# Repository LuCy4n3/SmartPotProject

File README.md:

# SmartPot / GreenGrowTech

An experimental smart plant-pot system combining a custom AVR board, an Android
app, a SQL Server database, a .NET API, a serial gateway and an optional camera.
The app displays plant and pot information and sends pump, greenhouse and photo
requests through the API to the connected hardware.

[Proof-of-concept video](https://www.youtube.com/watch?v=sH559vDkE20&t=21s&ab_channel=RaulSimonca)

## How the parts connect

```text
Android app <--> SQLserverFinale API <--> SQL Server (PlantsDB)
                         ^
                         | HTTP
                       potHub <--> serial/radio <--> SmartPot AVR board

Camera host <--> board UART; camera host --> API image upload
```

`potHub` is a console serial gateway. Although its project uses the web SDK and
has launch profiles, it does not start an HTTP server.

## Repository layout

| Directory | Contents |
| --- | --- |
| `AndroidApp/` | Java Android app (`com.example.greengrowtechapp`). |
| `SQLserverFinale/` | ASP.NET Core 8 API, Entity Framework models and migrations. |
| `potHub/` | .NET 8 serial-to-HTTP gateway for readings and control commands. |
| `SmartPotV4/` | Atmel/Microchip Studio solution with C and C++ firmware projects. |
| `PCB/` | KiCad board designs, component libraries, modules and manufacturing outputs. |
| `CameraCode/` | Python UART/camera scripts and legacy camera installation references. |
| `Programmer/` | Programming, serial, RS485 and demo utilities, including third-party code. |
| `I2CTests/` | Separate firmware experiments for sensors and I2C. |
| `proj_test/` | Supporting experiments and plant-data tools; not needed for normal startup. |

The root files `BackUpDataBase` and `DatabaseBackUp` are legacy SQL Server backup
files, despite having no extension. They are retained as database restore inputs.

The [SmartPot PCB overview](PCB/SmartPot/README.md) links the current editable
board, the separately preserved 2024-10-09 snapshot and the additional
manufacturing exports supplied with the local PCB collection.

## Requirements

- Windows with the .NET 8 SDK for the API and gateway.
- SQL Server or SQL Server LocalDB, plus a database administration tool such as
  SQL Server Management Studio (SSMS).
- Android Studio with JDK 17 and Android SDK 33. The project uses Android Gradle
  Plugin 8.1.0 and the included Gradle 8.0 wrapper. The app requires Android 12
  (API 31) or later.
- For hardware: the matching SmartPot PCB, serial/radio interface and
  Atmel/Microchip Studio with AVR32DA32 support and a compatible programmer.
- For the optional camera: a compatible Linux camera host, Python 3, an enabled
  UART and a working `libcamera-still` command.

Commands below run from the repository root in PowerShell unless stated otherwise.

## 1. Prepare the database

Restore a suitable root backup into a local database, for example `PlantsDB`.
In SSMS, use **Databases > Restore Database > Device**, browse to the backup file
(select all file types if necessary), and review the source database and file
destinations before restoring into a new database.

The API expects `Plant`, `User` and `Pot` tables. The checked-in migrations include
the original schema and a later change to make `PotId` an identity column. This
repository does not automatically create, migrate or seed the database at startup.
Use a restored database as the initial setup path; inspect migrations before
applying them to an existing database because `PotIdentity` drops and recreates
the `PotId` column.

Verify that the database contains the plant and user records you want to use.
A pot references an existing `PlantName` and `UserId`, and `PotName` must be unique.
Backup contents and record IDs may differ between the two backups.

## 2. Configure and start the API

For a fresh checkout, create the local configuration file once:

```powershell
Copy-Item SQLserverFinale/SQLserverFinale/appsettings.example.json SQLserverFinale/SQLserverFinale/appsettings.json
```

If `appsettings.json` already exists, keep it and edit the connection string for
your database instead. This local file is ignored by Git. The example uses
Windows authentication with LocalDB; use your own SQL Server connection string
when running a different instance.

An environment variable can override the connection string for the current shell:

```powershell
$env:ConnectionStrings__DefaultConnection = 'Server=(localdb)\MSSQLLocalDB;Database=PlantsDB;Integrated Security=True;TrustServerCertificate=True;'
```

Start the API on port 3000:

```powershell
dotnet restore SQLserverFinale/SQLserverFinale/SQLserverFinale.csproj
dotnet run --project SQLserverFinale/SQLserverFinale/SQLserverFinale.csproj --no-launch-profile --urls http://0.0.0.0:3000
```

This overrides the old machine-specific address in `launchSettings.json`. When
using an IDE launch profile instead, update that profile to your server's address.
Allow the chosen TCP port through the host firewall for LAN clients.

Check the running API in a second PowerShell window:

```powershell
Invoke-RestMethod http://localhost:3000/api/Plant
Invoke-RestMethod http://localhost:3000/api/Pot
```

Swagger is currently disabled in `Program.cs`, so `/swagger` is not a startup check.

## 3. Configure and run the Android app

1. Open `AndroidApp/` in Android Studio and let Gradle sync.
2. In `app/src/main/java/com/example/greengrowtechapp/MainActivity.java`, set
   `Url` to `http://<API_HOST>:3000/api/`, including the trailing slash. A physical
   phone needs the API computer's LAN address; `localhost` refers to the phone.
   The Android emulator normally reaches the host through `10.0.2.2`.
3. In `app/src/main/res/xml/network_security_config.xml`, add the same host
   without a scheme or port to the domains allowed to use HTTP.
4. Set `indexOfCurrentUser` to an existing database user. Its current source
   default is `303`; this must match the gateway's user for an integrated setup.
5. Ensure that user has at least one pot before starting the app: startup reads
   the first pot returned for that user. Set the initial pot ID consistently in
   `MainActivity.java` if needed.
6. Run the app on an Android 12+ phone or emulator. Use the plant/pot screens to
   view records, select a pot and send control requests.

You can also build a debug APK from PowerShell:

```powershell
Push-Location AndroidApp
.\gradlew.bat assembleDebug
Pop-Location
```

The APK is written to `AndroidApp/app/build/outputs/apk/debug/app-debug.apk`.

## 4. Configure the board and serial gateway

Open `SmartPotV4/SmartPotV4.atsln` in Atmel/Microchip Studio. The fuller sensor and
control implementation is `SmartPotV4_Cpp`; the sibling `SmartPotV4` C project
contains test code. Select the intended project explicitly before building or
flashing. Verify the target, board connections and programmer against the PCB.

In `SmartPotV4/SmartPotV4_Cpp/main.cpp`, `INDEX` is the pot identifier and `TYPE`
is the hardware type. The source currently uses `INDEX = 4` and `TYPE = 2`.
Match the firmware's pot ID to the database record. Do not assume a newly created
identity value equals the firmware's ID.

Before starting the gateway, edit `potHub/potHub/Program.cs`:

- Set `SerialPortStream("COM22", 9600)` to the actual interface and matching baud rate.
- Set **all four** `httpClient.BaseAddress` assignments to the API address, for
  example `http://localhost:3000` when both programs run on the same computer.
- Align `USER`, literal `UserId = 1` assignments and the hard-coded
  `/api/Pot/1/{index}` request with the Android user's database ID. Changing
  `USER` alone does not update all of these values.

These settings are currently in source code; the gateway does not read them from
`appsettings.json` or environment variables.

```powershell
dotnet restore potHub/potHub/potHub.csproj
dotnet run --project potHub/potHub/potHub.csproj --no-launch-profile
```

Start the API first, connect the serial interface, then start the gateway. The
gateway waits for the board's identification data. If it stays at `Looking for
data.`, check the serial port, baud rate and board transmission; reset the board
after opening the gateway if its startup identification was missed.

## 5. Optional camera

On the Linux camera host, confirm `libcamera-still` can capture a photo and the
UART is enabled. In `CameraCode/startup_uart.py`, set the serial device (currently
`/dev/ttyAMA0`, 9600 baud) and upload URL to your setup. The upload endpoint is
`http://<API_HOST>:3000/api/image/upload`.

Run from `CameraCode/` on that host:

```bash
python3 -m venv .venv
source .venv/bin/activate
python -m pip install -r requirements.txt
python startup_uart.py
```

This script reacts to UART bytes `0x15 0x01 0x05`, captures `test.jpg`, and uploads
it as multipart field `image`. The older `finalScript.py` checks decimal `15`
(`0x0F`) as its header instead, so these scripts are not interchangeable. Match
the script to the board's camera command; this needs hardware verification.
An uploaded `test.jpg` is available at `/api/image/test.jpg`.

The camera installation script and link lists are legacy hardware references.
Use a camera stack compatible with the actual camera and OS; the old ARM64 `.deb`
downloads are kept locally when cleaning an existing checkout and are ignored by Git.

## Troubleshooting and current limits

| Symptom | Check |
| --- | --- |
| API fails on database access | SQL instance, database restore, connection string and table names. |
| Phone cannot reach API | API host/port, LAN connection, firewall and Android HTTP domain list. |
| No pots or startup error in app | Existing user ID and at least one associated pot. |
| Gateway cannot open serial port | Correct device, port permissions and another program holding the port. |
| Readings or controls target the wrong pot | Firmware `INDEX`, database `PotId` and user IDs in every client. |
| Photo never arrives | Camera UART command/header, capture command and upload URL. |

This is a prototype with hard-coded network addresses and IDs. The current API
handles user passwords directly and does not implement production authentication;
use test accounts on a trusted development network. Camera integration and the
experimental NPK/SPI paths need verification on the target hardware. No end-to-end
hardware validation is implied by the repository cleanup.

## Git and local files

Track source code, project definitions, migrations, PCB designs and required
libraries. Build outputs, IDE state, camera-host home files, installed Python
packages, caches, KiCad locks/backups and local configuration are ignored.

For an existing checkout, cleanup removes generated and local files from Git's
index while leaving their working copies in place. The large
`Programmer/iot-sunxi-driver/` source tree is third-party code and is retained
with its original documentation and license. The original README also identifies
`Programmer/` as externally sourced; verify attribution before redistributing it.

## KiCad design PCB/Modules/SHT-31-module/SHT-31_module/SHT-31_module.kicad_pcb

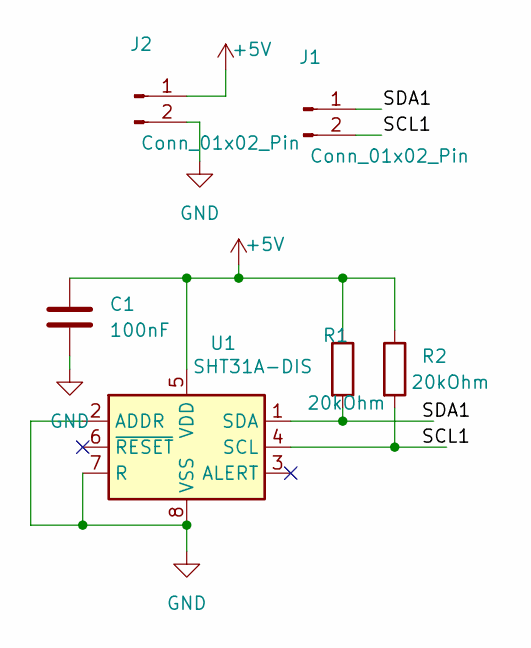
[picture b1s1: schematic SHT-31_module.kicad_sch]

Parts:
C1: 100nF; C_1206_3216Metric
J1, J2: Conn_01x02_Pin; PinHeader_1x02_P2.54mm_Vertical
R1, R2: 20kOhm; R_1206_3216Metric_Pad1.30x1.75mm_HandSolder
U1: SHT31A-DIS; Sensirion_DFN-8-1EP_2.5x2.5mm_P0.5mm_EP1.1x1.7mm

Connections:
+5V: C1.1, J2.1, R1.1, R2.1, U1.5 (VDD)
/SCL1: J1.2, R2.2, U1.4 (SCL)
/SDA1: J1.1, R1.2, U1.1 (SDA)
GND: C1.2, J2.2, U1.2 (ADDR), U1.7 (R), U1.8 (VSS), U1.9 (VSS)

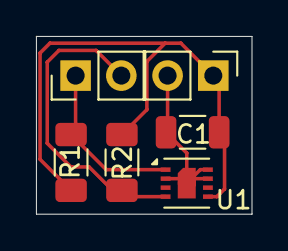
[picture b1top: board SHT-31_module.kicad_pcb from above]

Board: 2 copper layers, 12.0 x 9.9 mm, 6 parts (0 on the bottom side), 4 nets.

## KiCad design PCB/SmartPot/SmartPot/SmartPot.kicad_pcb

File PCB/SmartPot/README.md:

# SmartPot PCB files

| Location | Contents |
| --- | --- |
| [Current editable project](SmartPot/SmartPot.kicad_pro) | Existing tracked SmartPot schematic and PCB. |
| [2024-10-09 snapshot](revisions/2024-10-09/SmartPot.kicad_pro) | Editable schematic, PCB and project imported from the dated local backup. |
| `manufacturing/imported/GERBER/` | Additional supplied SmartPot manufacturing export. |
| `manufacturing/imported/grb/` | Additional supplied SmartPot manufacturing export and drill files. |
| `manufacturing/imported/drill/` | Supplied standalone plated/non-plated drill files. |

The dated snapshot differs from the current design and is kept separately.
The original tracked board was not overwritten. The manufacturing sets are
preserved as supplied; their correspondence to a particular editable revision
has not been established. Regenerate manufacturing output from the chosen PCB
revision when preparing a new fabrication run.

The snapshot comes from `SmartPot-2024-10-09_225239.zip`. The native source
filenames remain `SmartPot.kicad_pro`, `SmartPot.kicad_sch` and `SmartPot.kicad_pcb`.
Open the project file for the revision you want to inspect in KiCad.

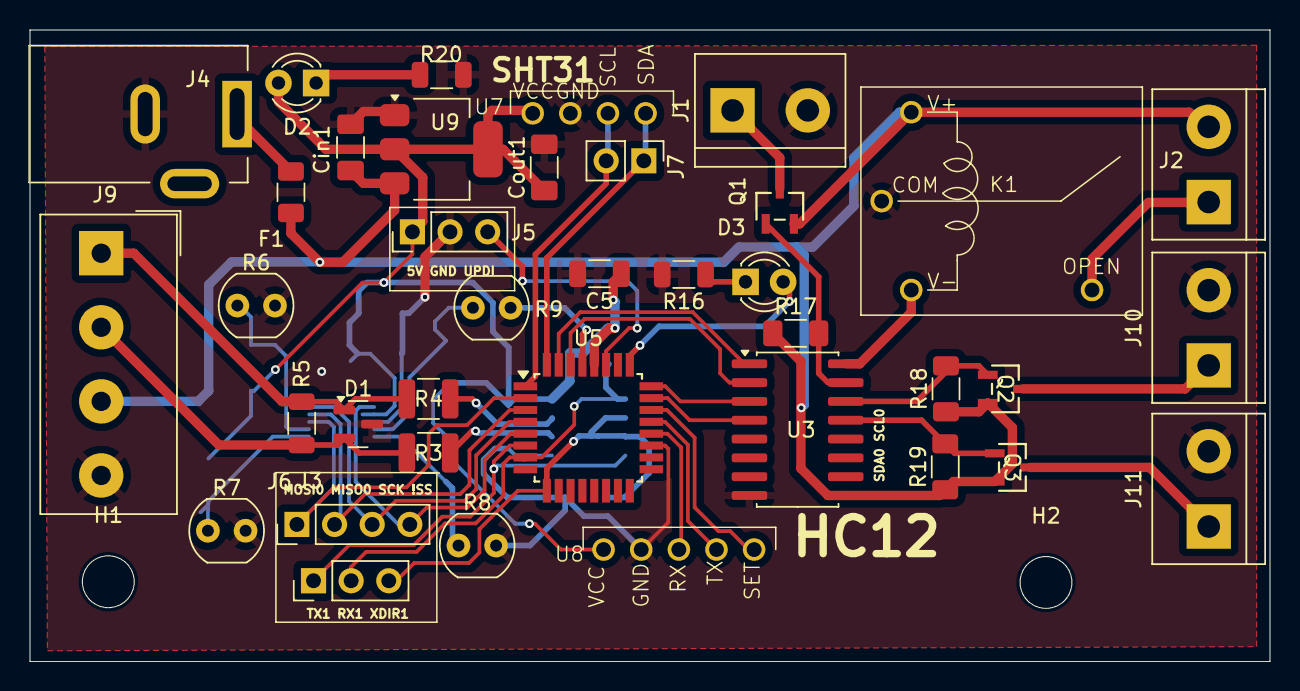
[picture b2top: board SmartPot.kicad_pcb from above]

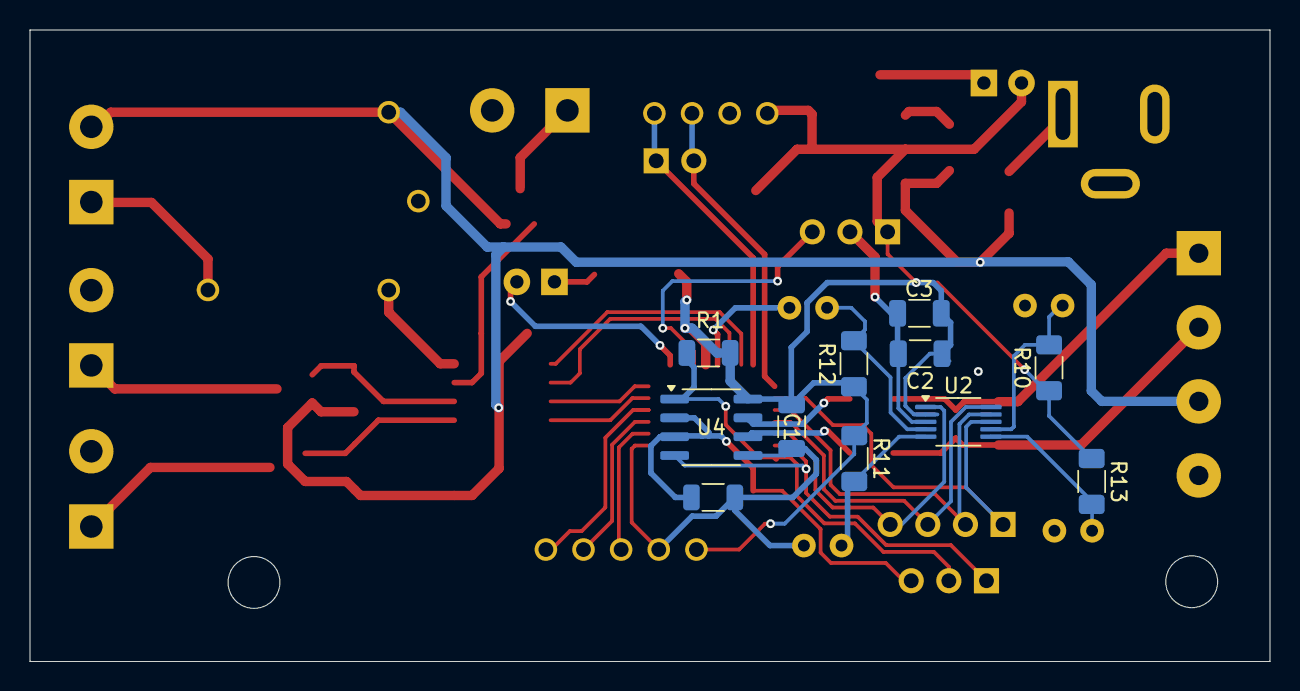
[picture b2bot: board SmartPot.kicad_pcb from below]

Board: 2 copper layers, 83.7 x 42.6 mm, 51 parts (11 on the bottom side), 40 nets.

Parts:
C1: 100nF; C_1206_3216Metric
C2: 0.1uF; C_1206_3216Metric
C3: 10uF; C_1206_3216Metric
C5: 1uF; C_1206_3216Metric
Cin1: 100nF; C_1206_3216Metric_Pad1.33x1.80mm_HandSolder
Cout1: 10uF; C_1206_3216Metric_Pad1.33x1.80mm_HandSolder
D1: SM712_SOT23; SOT-23
D2, D3: LED; LED_D3.0mm_FlatTop
F1: Fuse; Fuse_1206_3216Metric
H1, H2: MountingHole; MountingHole_3.5mm
J1, J2, J10, J11: Screw_Terminal_01x02; TerminalBlock_bornier-2_P5.08mm
J3, J5: Conn_01x03_Pin; PinHeader_1x03_P2.54mm_Vertical
J4: Barrel_Jack_MountingPin; BarrelJack_Kycon_KLDX-0202-xC_Horizontal
J6: Conn_01x04_Pin; PinHeader_1x04_P2.54mm_Vertical
J7: Conn_01x02_Pin; PinHeader_1x02_P2.54mm_Vertical
J9: Screw_Terminal_01x04; Altech_AK100_1x04_P5.00mm
K1: AWHSH112DM00G
Q1, Q2, Q3: SSM3J352F_LF; S-MINI_TOS
R1, R2: 10kOhm; R_1206_3216Metric
R3, R4: 10Ohm; R_1210_3225Metric
R5: 120; R_1206_3216Metric
R6, R7, R8, R9: R_Photo; R_LDR_4.9x4.2mm_P2.54mm_Vertical
R10, R17, R18, R19: 10kohm; R_1206_3216Metric_Pad1.30x1.75mm_HandSolder
R11, R13: 56.2kOhm; R_1206_3216Metric_Pad1.30x1.75mm_HandSolder
R12: 10kOhm; R_1206_3216Metric_Pad1.30x1.75mm_HandSolder
R16, R20: 250-400 Ohm; R_1206_3216Metric
U2: ADC084S021CIMM/NOPB; VSSOP-10_3x3mm_P0.5mm
U3: ULN2003A; SOIC-16W_5.3x10.2mm_P1.27mm
U4: THVD1400D; SOIC-8_3.9x4.9mm_P1.27mm
U5: AVR32DA32x-xPT; TQFP-32_7x7mm_P0.8mm
U7: SHT31-Module
U8: HC12-Modules
U9: LT1117-5.0; SOT-223-3_TabPin2

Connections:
+5V: C1.1, C2.1, C3.1, C5.1, Cout1.1, D2.2 (A), J5.1, R1.1, R10.1, R11.1, R12.1, R13.1, U2.2 (VA), U4.8 (VCC), U5.28 (VDD), U7.1 (VCC), U8.1 (VCC), U9.2 (VO)
+12V: Cin1.1, F1.1, J2.2, J9.3, K1.V+, Q1.2, Q2.2, Q3.2, R17.1, R18.1, R19.1, U3.9 (COM), U9.3 (VI)
/12Out: F1.2, J4.1
/!SS: J6.4, U2.1 (~CS), U5.5 (PA7)
/A: D1.2 (A2), J9.2, R3.2, R5.1
/Aout: R4.1, U4.7 (B)
/B: D1.1 (A1), J9.1, R4.2, R5.2
/Bout: R3.1, U4.6 (A)
/COMM1: U3.1 (I1), U5.31 (PA1)
/COMM2: U3.2 (I2), U5.30 (PA0)
/COMM3: U3.3 (I3), U5.24 (PF4)
/COMM4: U3.4 (I4), U5.23 (PF3)
/DIN: J6.1, U2.8 (DIN), U5.2 (PA4)
/IN1: R6.1, R10.2, U2.7 (IN1)
/IN2: R7.1, R13.2, U2.6 (IN2)
/IN3: R8.1, R11.2, U2.5 (IN3)
/IN4: R9.1, R12.2, U2.4 (IN4)
/LOAD1: J1.1, Q1.3
/LOAD2: J10.1, Q2.3
/LOAD3: J11.1, Q3.3
/MCLED: D3.2 (A), U5.25 (PF5)
/MISO0: J6.2, U2.9 (DOUT), U5.3 (PA5)
/OPEN: J2.1, K1.OPEN
/OUT1: K1.V-, U3.16 (O1)
/OUT2: Q1.1, R17.2, U3.15 (O2)
/OUT3: Q2.1, R18.2, U3.14 (O3)
/OUT4: Q3.1, R19.2, U3.13 (O4)
/RX1: J3.2, R1.2, U4.1 (RO), U5.7 (PC1)
/RX2: U5.21 (XTAL32K2/PF1), U8.4 (TX)
/SCK: J6.3, U2.10 (SCLK), U5.4 (PA6)
/SCL0: J7.2, U5.1 (PA3), U7.3 (SCL)
/SDA0: J7.1, U5.32 (PA2), U7.4 (SDA)
/SET: U5.22 (PF2), U8.5 (SET)
/TX1: J3.1, U4.4 (DI), U5.6 (PC0)
/TX2: U5.20 (XTAL32K1/PF0), U8.3 (RX)
/UPDI: J5.3, U5.27 (UPDI)
/XDIR1: J3.3, R2.1, U4.2 (~RE), U4.3 (DE), U5.9 (PC3)
GND: C1.2, C2.2, C3.2, C5.2, Cin1.2, Cout1.2, D1.3 (common), J1.2, J4.2, J5.2, J9.4, J10.2, J11.2, K1.COM, R2.2, R6.2, R7.2, R8.2, R9.2, R16.2, R20.2, U2.3 (GND), U3.8 (GND), U4.5 (GND), U5.19 (GND), U5.29 (GND), U7.2 (GND), U8.2 (GND), U9.1 (GND)
unnamed: D2.1 (K), R20.1
unnamed: D3.1 (K), R16.1

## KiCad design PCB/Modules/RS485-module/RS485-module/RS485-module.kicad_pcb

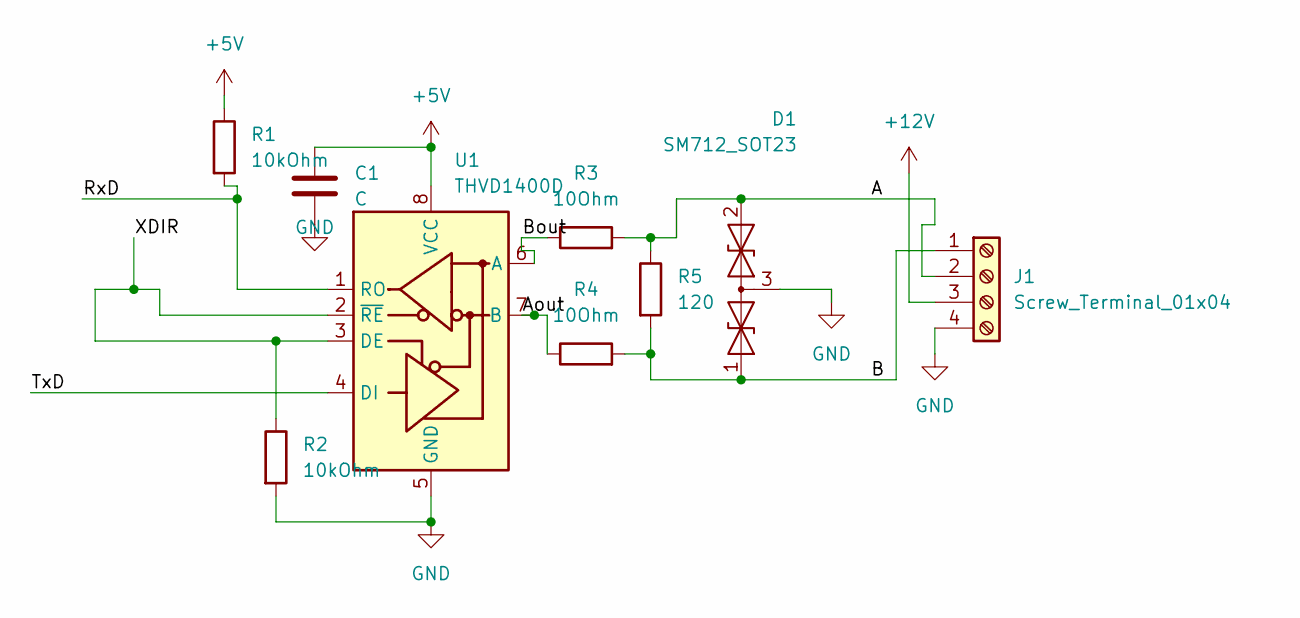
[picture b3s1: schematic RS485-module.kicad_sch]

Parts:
C1: C; C_1206_3216Metric
D1: SM712_SOT23; SOT-23
J1: Screw_Terminal_01x04; Altech_AK100_1x04_P5.00mm
R1, R2: 10kOhm; R_1206_3216Metric
R3, R4: 10Ohm; R_1210_3225Metric
R5: 120; R_1206_3216Metric
U1: THVD1400D; SOIC-8_3.9x4.9mm_P1.27mm

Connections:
+5V: C1.1, R1.1, U1.8 (VCC)
+12V: J1.3
/A: D1.2 (A2), J1.2, R3.2, R5.1
/Aout: R4.1, U1.7 (B)
/B: D1.1 (A1), J1.1, R4.2, R5.2
/Bout: R3.1, U1.6 (A)
/RxD: R1.2, U1.1 (RO)
/TxD: U1.4 (DI)
/XDIR: R2.1, U1.2 (~RE), U1.3 (DE)
GND: C1.2, D1.3 (common), J1.4, R2.2, U1.5 (GND)

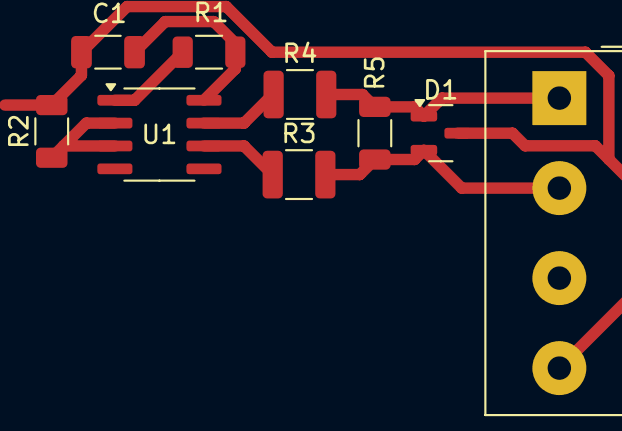
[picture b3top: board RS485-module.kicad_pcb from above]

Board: 2 copper layers, 9 parts (0 on the bottom side), 8 nets.

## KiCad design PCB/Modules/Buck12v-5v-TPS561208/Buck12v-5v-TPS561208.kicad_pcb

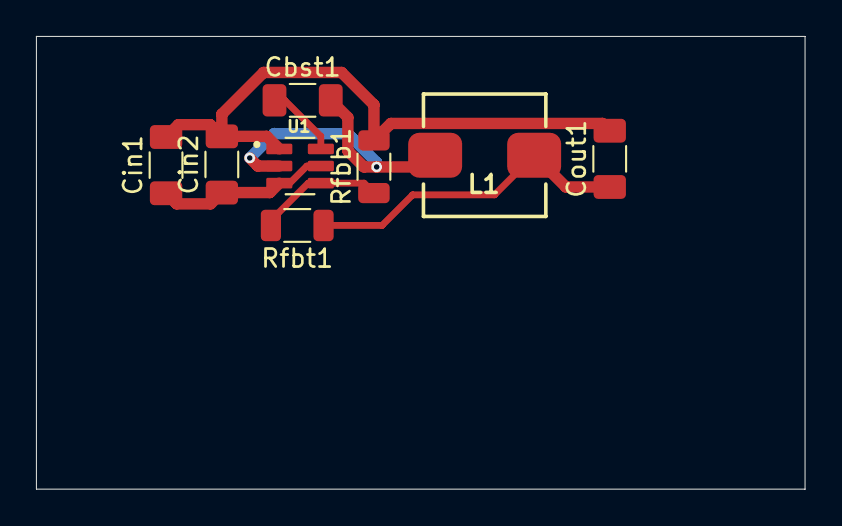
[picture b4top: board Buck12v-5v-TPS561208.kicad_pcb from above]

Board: 2 copper layers, 42.7 x 25.2 mm, 8 parts (0 on the bottom side), 6 nets.

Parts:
Cbst1: 100nF; C_1206_3216Metric_Pad1.33x1.80mm_HandSolder
Cin1, Cin2: 10uF; C_1206_3216Metric_Pad1.33x1.80mm_HandSolder
Cout1: 47uF; C_1206_3216Metric_Pad1.33x1.80mm_HandSolder
L1: 4.7uH; L_6.8x6.8_H3
Rfbb1: 10kOhm; R_1206_3216Metric
Rfbt1: 56.2kOhm; R_1206_3216Metric
U1: TPS561208DDCT; SOT95P280X110-6N

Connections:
+5V: Cout1.1, L1.2, Rfbt1.1
+12V: Cin1.1, Cin2.1, U1.3 (VIN), U1.5 (EN)
/SW: Cbst1.2, L1.1, U1.2 (SW)
/VBST: Cbst1.1, U1.6 (VBST)
/VFB: Rfbb1.1, Rfbt1.2, U1.4 (VFB)
GND: Cin1.2, Cin2.2, Cout1.2, Rfbb1.2, U1.1 (GND)

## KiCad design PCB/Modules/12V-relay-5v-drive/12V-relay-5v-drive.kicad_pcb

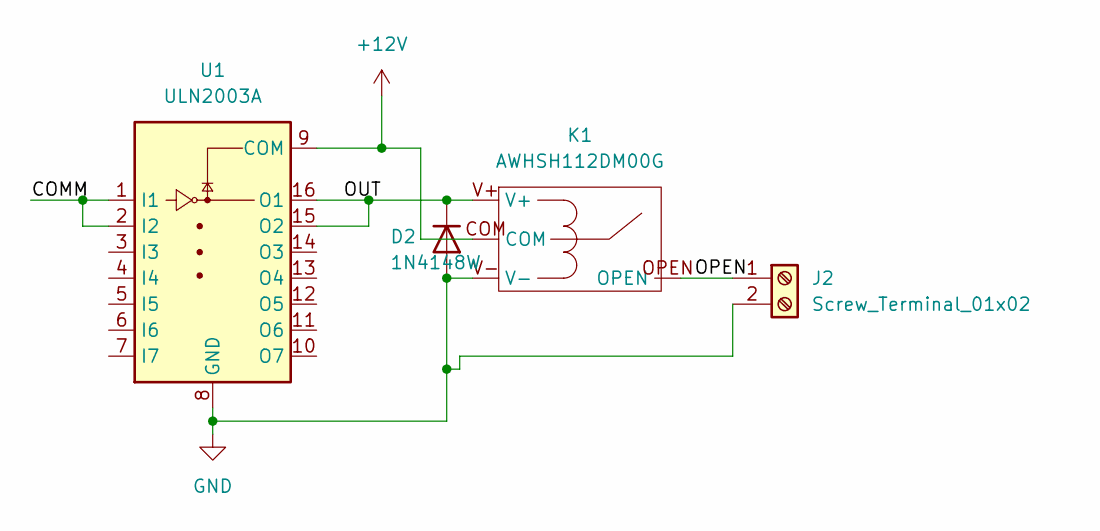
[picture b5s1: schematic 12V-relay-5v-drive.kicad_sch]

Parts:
D2: 1N4148W; D_SOD-123
J2: Screw_Terminal_01x02; TerminalBlock_bornier-2_P5.08mm
K1: AWHSH112DM00G
U1: ULN2003A; SOIC-16W_5.3x10.2mm_P1.27mm

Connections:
+12V: K1.COM, U1.9 (COM)
/COMM: U1.1 (I1), U1.2 (I2)
/OPEN: J2.1, K1.OPEN
/OUT: D2.1 (K), K1.V+, U1.15 (O2), U1.16 (O1)
GND: D2.2 (A), J2.2, K1.V-, U1.8 (GND)

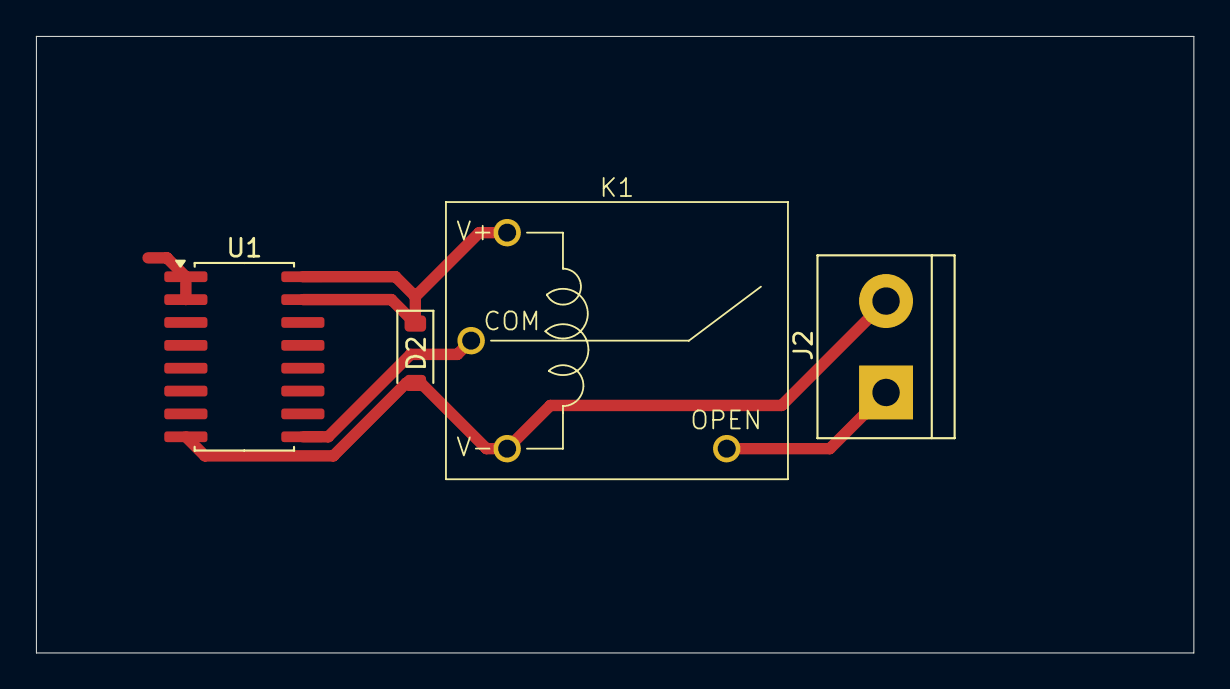
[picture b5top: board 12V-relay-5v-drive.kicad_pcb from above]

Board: 2 copper layers, 64.3 x 34.2 mm, 4 parts (0 on the bottom side), 5 nets.

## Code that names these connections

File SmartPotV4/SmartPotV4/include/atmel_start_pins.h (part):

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#include <port.h>

/**
 * \brief Set PA0 pull mode
 *
 * Configure pin to pull up, down or disable pull mode, supported pull
 * modes are defined by device used
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}

/**
 * \brief Set PA0 data direction
 *
 * Select if the pin data direction is input, output or disabled.
 * If disabled state is not possible, this function throws an assert.
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}

/**
 * \brief Set PA0 input/sense configuration
 *
 * Enable/disable PA0 digital input buffer and pin change interrupt,
 * select pin interrupt edge/level sensing mode
 *
 * \param[in] isc PORT_ISC_INTDISABLE_gc    = Iterrupt disabled but input buffer enabled
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}

/**
 * \brief Set PA0 inverted mode
 *
 * Enable or disable inverted I/O on a pin
 *
 * \param[in] inverted true  = I/O on PA0 is inverted
 *                     false = I/O on PA0 is not inverted
 */
static inline void PA0_set_inverted(const bool inverted)
{
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}

/**
 * \brief Set PA0 level
 *
 * Sets output level on a pin
 *
 * \param[in] level true  = Pin level set to "high" state
 *                  false = Pin level set to "low" state
 */
static inline void PA0_set_level(const bool level)
{
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}

/**
 * \brief Toggle output level on PA0
 *
 * Toggle the pin level
 */
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}

/**
 * \brief Get level on PA0
 *
 * Reads the level on a pin
 */
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}

/**
 * \brief Set PA2 pull mode
 *
 * Configure pin to pull up, down or disable pull mode, supported pull
 * modes are defined by device used
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}

/**
 * \brief Set PA2 data direction
 *
 * Select if the pin data direction is input, output or disabled.
 * If disabled state is not possible, this function throws an assert.
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}

/**
 * \brief Set PA2 input/sense configuration
 *
 * Enable/disable PA2 digital input buffer and pin change interrupt,
 * select pin interrupt edge/level sensing mode
 *
 * \param[in] isc PORT_ISC_INTDISABLE_gc    = Iterrupt disabled but input buffer enabled
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}

/**
 * \brief Set PA2 inverted mode
 *
 * Enable or disable inverted I/O on a pin
 *
 * \param[in] inverted true  = I/O on PA2 is inverted
 *                     false = I/O on PA2 is not inverted
 */
static inline void PA2_set_inverted(const bool inverted)
{
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}

/**
 * \brief Set PA2 level
 *
 * Sets output level on a pin
 *
 * \param[in] level true  = Pin level set to "high" state
 *                  false = Pin level set to "low" state
 */
static inline void PA2_set_level(const bool level)
{
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}

/**
 * \brief Toggle output level on PA2
 *
 * Toggle the pin level
 */
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}

/**
 * \brief Get level on PA2
 *
 * Reads the level on a pin
 */
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}

/**
 * \brief Set PA3 pull mode
 *
 * Configure pin to pull up, down or disable pull mode, supported pull
 * modes are defined by device used
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}

/**
 * \brief Set PA3 data direction
 *
 * Select if the pin data direction is input, output or disabled.
 * If disabled state is not possible, this function throws an assert.
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}

/**
 * \brief Set PA3 input/sense configuration
 *
 * Enable/disable PA3 digital input buffer and pin change interrupt,
 * select pin interrupt edge/level sensing mode
 *
 * \param[in] isc PORT_ISC_INTDISABLE_gc    = Iterrupt disabled but input buffer enabled
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}

/**
 * \brief Set PA3 inverted mode
 *
 * Enable or disable inverted I/O on a pin
 *
 * \param[in] inverted true  = I/O on PA3 is inverted
 *                     false = I/O on PA3 is not inverted
 */
static inline void PA3_set_inverted(const bool inverted)
{
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}

/**
 * \brief Set PA3 level
 *
 * Sets output level on a pin
 *
 * \param[in] level true  = Pin level set to "high" state
 *                  false = Pin level set to "low" state
 */
static inline void PA3_set_level(const bool level)
{
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}

/**
 * \brief Toggle output level on PA3
 *
 * Toggle the pin level
 */
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}

/**
 * \brief Get level on PA3
 *
 * Reads the level on a pin
 */
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}

/**
 * \brief Set PC0 pull mode
 *
 * Configure pin to pull up, down or disable pull mode, supported pull
 * modes are defined by device used
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}

/**
 * \brief Set PC0 data direction
 *
 * Select if the pin data direction is input, output or disabled.
 * If disabled state is not possible, this function throws an assert.
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}

/**
 * \brief Set PC0 input/sense configuration
 *
 * Enable/disable PC0 digital input buffer and pin change interrupt,
 * select pin interrupt edge/level sensing mode
 *
 * \param[in] isc PORT_ISC_INTDISABLE_gc    = Iterrupt disabled but input buffer enabled
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}

/**
 * \brief Set PC0 inverted mode
 *
 * Enable or disable inverted I/O on a pin
 *
 * \param[in] inverted true  = I/O on PC0 is inverted
 *                     false = I/O on PC0 is not inverted
 */
static inline void PC0_set_inverted(const bool inverted)
{
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}

/**
 * \brief Set PC0 level
 *
 * Sets output level on a pin
 *
 * \param[in] level true  = Pin level set to "high" state
 *                  false = Pin level set to "low" state
 */
static inline void PC0_set_level(const bool level)
{
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}

/**
 * \brief Toggle output level on PC0
 *
 * Toggle the pin level
 */
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}

/**
 * \brief Get level on PC0
 *
 * Reads the level on a pin
 */
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}

/**
 * \brief Set PC1 pull mode
 *
 * Configure pin to pull up, down or disable pull mode, supported pull
 * modes are defined by device used
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}

/**
 * \brief Set PC1 data direction
 *
 * Select if the pin data direction is input, output or disabled.
 * If disabled state is not possible, this function throws an assert.
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}

/**
 * \brief Set PC1 input/sense configuration
 *
 * Enable/disable PC1 digital input buffer and pin change interrupt,
 * select pin interrupt edge/level sensing mode
 *
 * \param[in] isc PORT_ISC_INTDISABLE_gc    = Iterrupt disabled but input buffer enabled
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}

/**
 * \brief Set PC1 inverted mode
 *
 * Enable or disable inverted I/O on a pin
 *
 * \param[in] inverted true  = I/O on PC1 is inverted
 *                     false = I/O on PC1 is not inverted
 */
static inline void PC1_set_inverted(const bool inverted)
{
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}

/**
 * \brief Set PC1 level
 *
 * Sets output level on a pin
 *
 * \param[in] level true  = Pin level set to "high" state
 *                  false = Pin level set to "low" state
 */
static inline void PC1_set_level(const bool level)
{
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}

/**
 * \brief Toggle output level on PC1
 *
 * Toggle the pin level
 */
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}

/**
 * \brief Get level on PC1
 *
 * Reads the level on a pin
 */
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}

/**
 * \brief Set PF0 pull mode
 *
 * Configure pin to pull up, down or disable pull mode, supported pull
 * modes are defined by device used
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}

/**
 * \brief Set PF0 data direction
 *
 * Select if the pin data direction is input, output or disabled.
 * If disabled state is not possible, this function throws an assert.
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}

/**
 * \brief Set PF0 input/sense configuration
 *
 * Enable/disable PF0 digital input buffer and pin change interrupt,
 * select pin interrupt edge/level sensing mode
 *
 * \param[in] isc PORT_ISC_INTDISABLE_gc    = Iterrupt disabled but input buffer enabled
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}

/**
 * \brief Set PF0 inverted mode
 *
 * Enable or disable inverted I/O on a pin
 *
 * \param[in] inverted true  = I/O on PF0 is inverted
 *                     false = I/O on PF0 is not inverted
 */
static inline void PF0_set_inverted(const bool inverted)
{
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}

/**
 * \brief Set PF0 level
 *
 * Sets output level on a pin
 *
 * \param[in] level true  = Pin level set to "high" state
 *                  false = Pin level set to "low" state
 */
static inline void PF0_set_level(const bool level)
{
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}

/**
 * \brief Toggle output level on PF0
 *
 * Toggle the pin level
 */
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}

/**
 * \brief Get level on PF0
 *
 * Reads the level on a pin
 */
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}

/**
 * \brief Set PF1 pull mode
 *
 * Configure pin to pull up, down or disable pull mode, supported pull
 * modes are defined by device used
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}

/**
 * \brief Set PF1 data direction
 *
 * Select if the pin data direction is input, output or disabled.
 * If disabled state is not possible, this function throws an assert.
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}

/**
 * \brief Set PF1 input/sense configuration
 *
 * Enable/disable PF1 digital input buffer and pin change interrupt,
 * select pin interrupt edge/level sensing mode
 *
 * \param[in] isc PORT_ISC_INTDISABLE_gc    = Iterrupt disabled but input buffer enabled
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}

/**
 * \brief Set PF1 inverted mode
 *
 * Enable or disable inverted I/O on a pin
 *
 * \param[in] inverted true  = I/O on PF1 is inverted
 *                     false = I/O on PF1 is not inverted
 */
static inline void PF1_set_inverted(const bool inverted)
{
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}

/**
 * \brief Set PF1 level
 *
 * Sets output level on a pin
 *
 * \param[in] level true  = Pin level set to "high" state
 *                  false = Pin level set to "low" state
 */
static inline void PF1_set_level(const bool level)
{
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}

/**
 * \brief Toggle output level on PF1
 *
 * Toggle the pin level
 */
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}

/**
 * \brief Get level on PF1
 *
 * Reads the level on a pin
 */
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}

/**
 * \brief Set PF2 pull mode
 *
 * Configure pin to pull up, down or disable pull mode, supported pull
 * modes are defined by device used
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}

/**
 * \brief Set PF2 data direction
 *
 * Select if the pin data direction is input, output or disabled.
 * If disabled state is not possible, this function throws an assert.
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}

/**
 * \brief Set PF2 input/sense configuration
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
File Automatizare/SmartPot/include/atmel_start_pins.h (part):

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#include <port.h>

/**
 * \brief Set PA2 pull mode
 *
 * Configure pin to pull up, down or disable pull mode, supported pull
 * modes are defined by device used
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}

/**
 * \brief Set PA2 data direction
 *
 * Select if the pin data direction is input, output or disabled.
 * If disabled state is not possible, this function throws an assert.
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}

/**
 * \brief Set PA2 input/sense configuration
 *
 * Enable/disable PA2 digital input buffer and pin change interrupt,
 * select pin interrupt edge/level sensing mode
 *
 * \param[in] isc PORT_ISC_INTDISABLE_gc    = Iterrupt disabled but input buffer enabled
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}

/**
 * \brief Set PA2 inverted mode
 *
 * Enable or disable inverted I/O on a pin
 *
 * \param[in] inverted true  = I/O on PA2 is inverted
 *                     false = I/O on PA2 is not inverted
 */
static inline void PA2_set_inverted(const bool inverted)
{
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}

/**
 * \brief Set PA2 level
 *
 * Sets output level on a pin
 *
 * \param[in] level true  = Pin level set to "high" state
 *                  false = Pin level set to "low" state
 */
static inline void PA2_set_level(const bool level)
{
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}

/**
 * \brief Toggle output level on PA2
 *
 * Toggle the pin level
 */
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}

/**
 * \brief Get level on PA2
 *
 * Reads the level on a pin
 */
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}

/**
 * \brief Set PA3 pull mode
 *
 * Configure pin to pull up, down or disable pull mode, supported pull
 * modes are defined by device used
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}

/**
 * \brief Set PA3 data direction
 *
 * Select if the pin data direction is input, output or disabled.
 * If disabled state is not possible, this function throws an assert.
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}

/**
 * \brief Set PA3 input/sense configuration
 *
 * Enable/disable PA3 digital input buffer and pin change interrupt,
 * select pin interrupt edge/level sensing mode
 *
 * \param[in] isc PORT_ISC_INTDISABLE_gc    = Iterrupt disabled but input buffer enabled
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}

/**
 * \brief Set PA3 inverted mode
 *
 * Enable or disable inverted I/O on a pin
 *
 * \param[in] inverted true  = I/O on PA3 is inverted
 *                     false = I/O on PA3 is not inverted
 */
static inline void PA3_set_inverted(const bool inverted)
{
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}

/**
 * \brief Set PA3 level
 *
 * Sets output level on a pin
 *
 * \param[in] level true  = Pin level set to "high" state
 *                  false = Pin level set to "low" state
 */
static inline void PA3_set_level(const bool level)
{
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}

/**
 * \brief Toggle output level on PA3
 *
 * Toggle the pin level
 */
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}

/**
 * \brief Get level on PA3
 *
 * Reads the level on a pin
 */
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}

/**
 * \brief Set PA4 pull mode
 *
 * Configure pin to pull up, down or disable pull mode, supported pull
 * modes are defined by device used
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}

/**
 * \brief Set PA4 data direction
 *
 * Select if the pin data direction is input, output or disabled.
 * If disabled state is not possible, this function throws an assert.
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}

/**
 * \brief Set PA4 input/sense configuration
 *
 * Enable/disable PA4 digital input buffer and pin change interrupt,
 * select pin interrupt edge/level sensing mode
 *
 * \param[in] isc PORT_ISC_INTDISABLE_gc    = Iterrupt disabled but input buffer enabled
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}

/**
 * \brief Set PA4 inverted mode
 *
 * Enable or disable inverted I/O on a pin
 *
 * \param[in] inverted true  = I/O on PA4 is inverted
 *                     false = I/O on PA4 is not inverted
 */
static inline void PA4_set_inverted(const bool inverted)
{
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}

/**
 * \brief Set PA4 level
 *
 * Sets output level on a pin
 *
 * \param[in] level true  = Pin level set to "high" state
 *                  false = Pin level set to "low" state
 */
static inline void PA4_set_level(const bool level)
{
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}

/**
 * \brief Toggle output level on PA4
 *
 * Toggle the pin level
 */
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}

/**
 * \brief Get level on PA4
 *
 * Reads the level on a pin
 */
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}

/**
 * \brief Set PC0 pull mode
 *
 * Configure pin to pull up, down or disable pull mode, supported pull
 * modes are defined by device used
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}

/**
 * \brief Set PC0 data direction
 *
 * Select if the pin data direction is input, output or disabled.
 * If disabled state is not possible, this function throws an assert.
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}

/**
 * \brief Set PC0 input/sense configuration
 *
 * Enable/disable PC0 digital input buffer and pin change interrupt,
 * select pin interrupt edge/level sensing mode
 *
 * \param[in] isc PORT_ISC_INTDISABLE_gc    = Iterrupt disabled but input buffer enabled
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}

/**
 * \brief Set PC0 inverted mode
 *
 * Enable or disable inverted I/O on a pin
 *
 * \param[in] inverted true  = I/O on PC0 is inverted
 *                     false = I/O on PC0 is not inverted
 */
static inline void PC0_set_inverted(const bool inverted)
{
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}

/**
 * \brief Set PC0 level
 *
 * Sets output level on a pin
 *
 * \param[in] level true  = Pin level set to "high" state
 *                  false = Pin level set to "low" state
 */
static inline void PC0_set_level(const bool level)
{
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}

/**
 * \brief Toggle output level on PC0
 *
 * Toggle the pin level
 */
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}

/**
 * \brief Get level on PC0
 *
 * Reads the level on a pin
 */
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}

/**
 * \brief Set PC1 pull mode
 *
 * Configure pin to pull up, down or disable pull mode, supported pull
 * modes are defined by device used
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}

/**
 * \brief Set PC1 data direction
 *
 * Select if the pin data direction is input, output or disabled.
 * If disabled state is not possible, this function throws an assert.
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}

/**
 * \brief Set PC1 input/sense configuration
 *
 * Enable/disable PC1 digital input buffer and pin change interrupt,
 * select pin interrupt edge/level sensing mode
 *
 * \param[in] isc PORT_ISC_INTDISABLE_gc    = Iterrupt disabled but input buffer enabled
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}

/**
 * \brief Set PC1 inverted mode
 *
 * Enable or disable inverted I/O on a pin
 *
 * \param[in] inverted true  = I/O on PC1 is inverted
 *                     false = I/O on PC1 is not inverted
 */
static inline void PC1_set_inverted(const bool inverted)
{
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}

/**
 * \brief Set PC1 level
 *
 * Sets output level on a pin
 *
 * \param[in] level true  = Pin level set to "high" state
 *                  false = Pin level set to "low" state
 */
static inline void PC1_set_level(const bool level)
{
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}

/**
 * \brief Toggle output level on PC1
 *
 * Toggle the pin level
 */
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}

/**
 * \brief Get level on PC1
 *
 * Reads the level on a pin
 */
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}

/**
 * \brief Set PC2 pull mode
 *
 * Configure pin to pull up, down or disable pull mode, supported pull
 * modes are defined by device used
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}

/**
 * \brief Set PC2 data direction
 *
 * Select if the pin data direction is input, output or disabled.
 * If disabled state is not possible, this function throws an assert.
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}

/**
 * \brief Set PC2 input/sense configuration
 *
 * Enable/disable PC2 digital input buffer and pin change interrupt,
 * select pin interrupt edge/level sensing mode
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}

/**
 * \brief Set PC2 inverted mode
 *
 * Enable or disable inverted I/O on a pin
 *
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}

/**
 * \brief Set PC2 level
 *
 * Sets output level on a pin
 *
 * \param[in] level true  = Pin level set to "high" state
 *                  false = Pin level set to "low" state
 */
static inline void PC2_set_level(const bool level)
{
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}

/**
 * \brief Set PC3 pull mode
 *
 * Configure pin to pull up, down or disable pull mode, supported pull
 * modes are defined by device used
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}

/**
 * \brief Set PC3 data direction
 *
 * Select if the pin data direction is input, output or disabled.
 * If disabled state is not possible, this function throws an assert.
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}

/**
 * \brief Set PC3 input/sense configuration
 *
 * Enable/disable PC3 digital input buffer and pin change interrupt,
 * select pin interrupt edge/level sensing mode
 *
 * \param[in] isc PORT_ISC_INTDISABLE_gc    = Iterrupt disabled but input buffer enabled
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}

/**
 * \brief Set PC3 inverted mode
 *
 * Enable or disable inverted I/O on a pin
 *
 * \param[in] inverted true  = I/O on PC3 is inverted
 *                     false = I/O on PC3 is not inverted
 */
static inline void PC3_set_inverted(const bool inverted)
{
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}

/**
 * \brief Set PC3 level
 *
 * Sets output level on a pin
 *
 * \param[in] level true  = Pin level set to "high" state
 *                  false = Pin level set to "low" state
 */
static inline void PC3_set_level(const bool level)
{
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}

/**
 * \brief Toggle output level on PC3
 *
 * Toggle the pin level
 */
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}

/**
 * \brief Get level on PC3
 *
 * Reads the level on a pin
 */
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}

/**
 * \brief Set PD0 pull mode
 *
 * Configure pin to pull up, down or disable pull mode, supported pull
 * modes are defined by device used
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}

/**
 * \brief Set PD0 data direction
 *
 * Select if the pin data direction is input, output or disabled.
 * If disabled state is not possible, this function throws an assert.
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}

/**
 * \brief Set PD0 input/sense configuration
 *
 * Enable/disable PD0 digital input buffer and pin change interrupt,
 * select pin interrupt edge/level sensing mode
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}

/**
 * \brief Set PD0 inverted mode
 *
 * Enable or disable inverted I/O on a pin
 *
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}

/**
 * \brief Set PD0 level
 *
 * Sets output level on a pin
 *
 * \param[in] level true  = Pin level set to "high" state
 *                  false = Pin level set to "low" state
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
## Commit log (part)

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2024-04-02 Search menu works, /pots is still not a sql server entity
2024-04-04 meniu funct, req fucntioneaza
2024-05-14 Plant DB works, Pot DB doesnt show up on the SQL server app
2024-05-15 added pot TB and it works with the API,it has a foreign key with Plant TB
2024-06-01 server finale has basic user and final pot
2024-06-01 smart pot first push
2024-06-01 Fixed compilation errors
2024-06-01 Removed files that should not be on git
2024-06-01 Added git ignore
2024-06-01 Added debug code
2024-06-07 SHT31
2024-06-07 Added programmer debugger (serial debugger)
2024-06-07 schimbari minore
2024-07-04 send temp and hum trough hex, added potHub and small changes overall
2024-07-05 potHub chnages
    cleaned up the code, tried to make it work with main server NOT TESTED YET
2024-07-05 small changes to how msg are sent from the board, changed potHub to work with current board and tested it with the app. Everything WORKS!
2024-07-21 ISR reading works, works with Postman. To-do: full app rework and server rework for security.
2024-08-16 New app being build on. Comppleted the getJson req. TODO: choosing between pots and adding pots
2024-08-17 Everything functional. TODO:implement camera fucntion and user login
2024-08-25 Commit after analog
2024-08-28 Re doing some elements of the databasae so it makes more sense and its better secured
2024-09-06 Getting pictures work. Updated hub code a bit. Need soldi script for raspberry.Everythimg works:getting pictures, getting pot data etc.
2024-09-10 post del changes
2024-09-10 test
2024-09-10 last commit on newAppBranch before merge
2024-10-11 Added PCB layout
2024-10-11 Added buck design
2024-10-12 Added new components and modules
2024-10-13 Small new changes
2024-10-13 Test kicad
2024-10-14 Added switch modules and RS485 module
2024-10-25 Finalized the v4 of the PCB and added the web scraper test codes
2024-11-03 Perfected the scarping bot and added plants dir where all plants will be added as excel files
2024-11-18 Added SmartPotV4 file for the new PCB. Small cghanges to the database(added new fields for plants and deleted plantId field). Big changes to the python script for webscrapping and AI. It works well. 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
2024-12-20 Finnished scraping. Backed up Db in BackUpDataBase, old back up should be updated to the new one. Deleted SmartPotV4 for remake.
2025-02-28 Modified the MCU code. To do: get ready for IoT competition. This version should have working UART irq with custom handlers for irq and working-ish SPI BitBang(tested with osciloscope)
2025-03-02 Added code fro rasp zero and updated the PCB
2025-03-09 Changed the server to send plant data in chunks(much needed) and working on the menu to select plants on android. Over all the chunk data works, need to make it clickable
2025-03-09 Menu works fine, to do: add actual add pot functions
2025-03-10 Pot menu works, to do: add delete option and think about the UI design.
2025-03-13 Added user menu delete and working on add pot. Created Test plant and made some changes on SPI software, that might actually work.
2025-03-13 Every menu works (del, automatic pot select, add pot). To do: Add login. :(
2025-03-18 Everything except NPK works. Should work fine for Iot.
2025-03-23 Push for final code for IoT
2025-09-25 Random commit
